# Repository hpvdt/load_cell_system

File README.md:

# Load Cell System

System to read up to six load cells and broadcast the data over USB to a host computer that would display and record it. Designed originally for testing wings for our wing profiles for lift and drag.

Hardware designed in KiCad, programmed using Arduino. Code depends on the HX711 library by [bodge](https://github.com/bogde/HX711).

The interface for the host computer is located in our [interfaces repository](https://github.com/hpvdt/interfaces) as `wing_tester`, and is based on Processing 3.

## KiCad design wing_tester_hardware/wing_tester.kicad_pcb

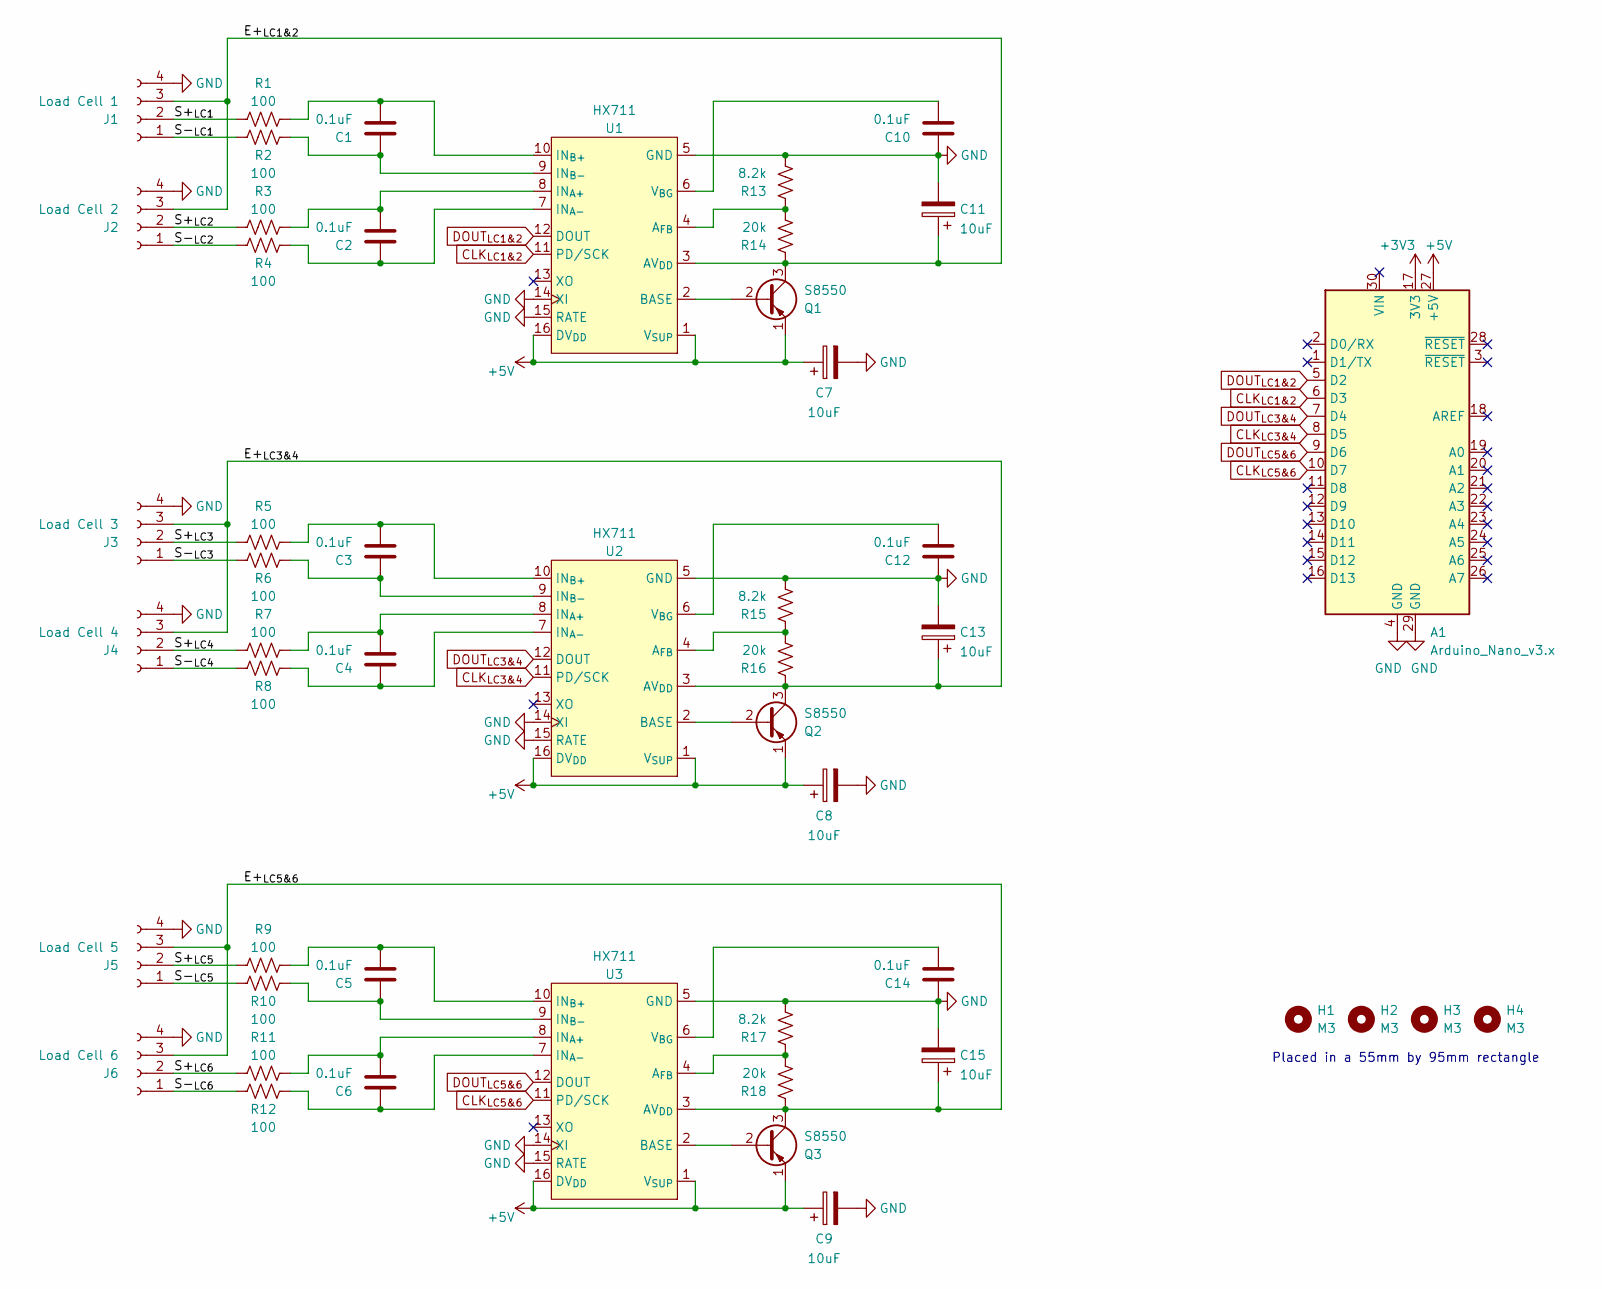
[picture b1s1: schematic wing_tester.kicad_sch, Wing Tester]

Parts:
A1: Arduino_Nano_v3.x; Arduino_Nano
C1, C2, C3, C4, C5, C6, C10, C12, C14: 0.1uF; CP_Radial_D5.0mm_P2.50mm
C7, C8, C9, C11, C13, C15: 10uF; CP_Radial_D5.0mm_P2.50mm
H1, H2, H3, H4: M3; MountingHole_3.2mm_M3_ISO7380_Pad
J1: Load Cell 1; PinHeader_1x04_P2.54mm_Vertical
J2: Load Cell 2; PinHeader_1x04_P2.54mm_Vertical
J3: Load Cell 3; PinHeader_1x04_P2.54mm_Vertical
J4: Load Cell 4; PinHeader_1x04_P2.54mm_Vertical
J5: Load Cell 5; PinHeader_1x04_P2.54mm_Vertical
J6: Load Cell 6; PinHeader_1x04_P2.54mm_Vertical
Q1, Q2, Q3: S8550; TO-92_Inline
R1, R2, R3, R4, R5, R6, R7, R8, R9, R10, R11, R12: 100; R_Axial_DIN0207_L6.3mm_D2.5mm_P10.16mm_Horizontal
R13, R15, R17: 8.2k; R_Axial_DIN0207_L6.3mm_D2.5mm_P10.16mm_Horizontal
R14, R16, R18: 20k; R_Axial_DIN0207_L6.3mm_D2.5mm_P10.16mm_Horizontal
U1, U2, U3: HX711; SOP-16_3.9x9.9mm_P1.27mm

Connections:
+3V3: A1.17 (3V3)
+5V: A1.27 (+5V), C7.1, C8.1, C9.1, Q1.1 (E), Q2.1 (E), Q3.1 (E), U1.1 (V_{SUP}), U1.16 (DV_{DD}), U2.1 (V_{SUP}), U2.16 (DV_{DD}), U3.1 (V_{SUP}), U3.16 (DV_{DD})
/E+_{LC1&2}: C11.1, J1.3, J2.3, Q1.3 (C), R14.1, U1.3 (AV_{DD})
/E+_{LC3&4}: C13.1, J3.3, J4.3, Q2.3 (C), R16.1, U2.3 (AV_{DD})
/E+_{LC5&6}: C15.1, J5.3, J6.3, Q3.3 (C), R18.1, U3.3 (AV_{DD})
/S+_{LC1}: J1.2, R1.1
/S+_{LC2}: J2.2, R3.1
/S+_{LC3}: J3.2, R5.1
/S+_{LC4}: J4.2, R7.1
/S+_{LC5}: J5.2, R9.1
/S+_{LC6}: J6.2, R11.1
/S-_{LC1}: J1.1, R2.1
/S-_{LC2}: J2.1, R4.1
/S-_{LC3}: J3.1, R6.1
/S-_{LC4}: J4.1, R8.1
/S-_{LC5}: J5.1, R10.1
/S-_{LC6}: J6.1, R12.1
CLK_{LC1&2}: A1.6 (D3), U1.11 (PD/SCK)
CLK_{LC3&4}: A1.8 (D5), U2.11 (PD/SCK)
CLK_{LC5&6}: A1.10 (D7), U3.11 (PD/SCK)
DOUT_{LC1&2}: A1.5 (D2), U1.12 (DOUT)
DOUT_{LC3&4}: A1.7 (D4), U2.12 (DOUT)
DOUT_{LC5&6}: A1.9 (D6), U3.12 (DOUT)
GND: A1.4 (GND), A1.29 (GND), C7.2, C8.2, C9.2, C10.2, C11.2, C12.2, C13.2, C14.2, C15.2, J1.4, J2.4, J3.4, J4.4, J5.4, J6.4, R13.2, R15.2, R17.2, U1.5 (GND), U1.14 (XI), U1.15 (RATE), U2.5 (GND), U2.14 (XI), U2.15 (RATE), U3.5 (GND), U3.14 (XI), U3.15 (RATE)
unnamed: C1.1, R1.2, U1.10 (IN_{B+})
unnamed: C1.2, R2.2, U1.9 (IN_{B-})
unnamed: C2.1, R3.2, U1.8 (IN_{A+})
unnamed: C2.2, R4.2, U1.7 (IN_{A-})
unnamed: C3.1, R5.2, U2.10 (IN_{B+})
unnamed: C3.2, R6.2, U2.9 (IN_{B-})
unnamed: C4.1, R7.2, U2.8 (IN_{A+})
unnamed: C4.2, R8.2, U2.7 (IN_{A-})
unnamed: C5.1, R9.2, U3.10 (IN_{B+})
unnamed: C5.2, R10.2, U3.9 (IN_{B-})
unnamed: C6.1, R11.2, U3.8 (IN_{A+})
unnamed: C6.2, R12.2, U3.7 (IN_{A-})
unnamed: C10.1, U1.6 (V_{BG})
unnamed: C12.1, U2.6 (V_{BG})
unnamed: C14.1, U3.6 (V_{BG})
unnamed: Q1.2 (B), U1.2 (BASE)
unnamed: Q2.2 (B), U2.2 (BASE)
unnamed: Q3.2 (B), U3.2 (BASE)
unnamed: R13.1, R14.2, U1.4 (A_{FB})
unnamed: R15.1, R16.2, U2.4 (A_{FB})
unnamed: R17.1, R18.2, U3.4 (A_{FB})

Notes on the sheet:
Placed in a 55mm by 95mm rectangle

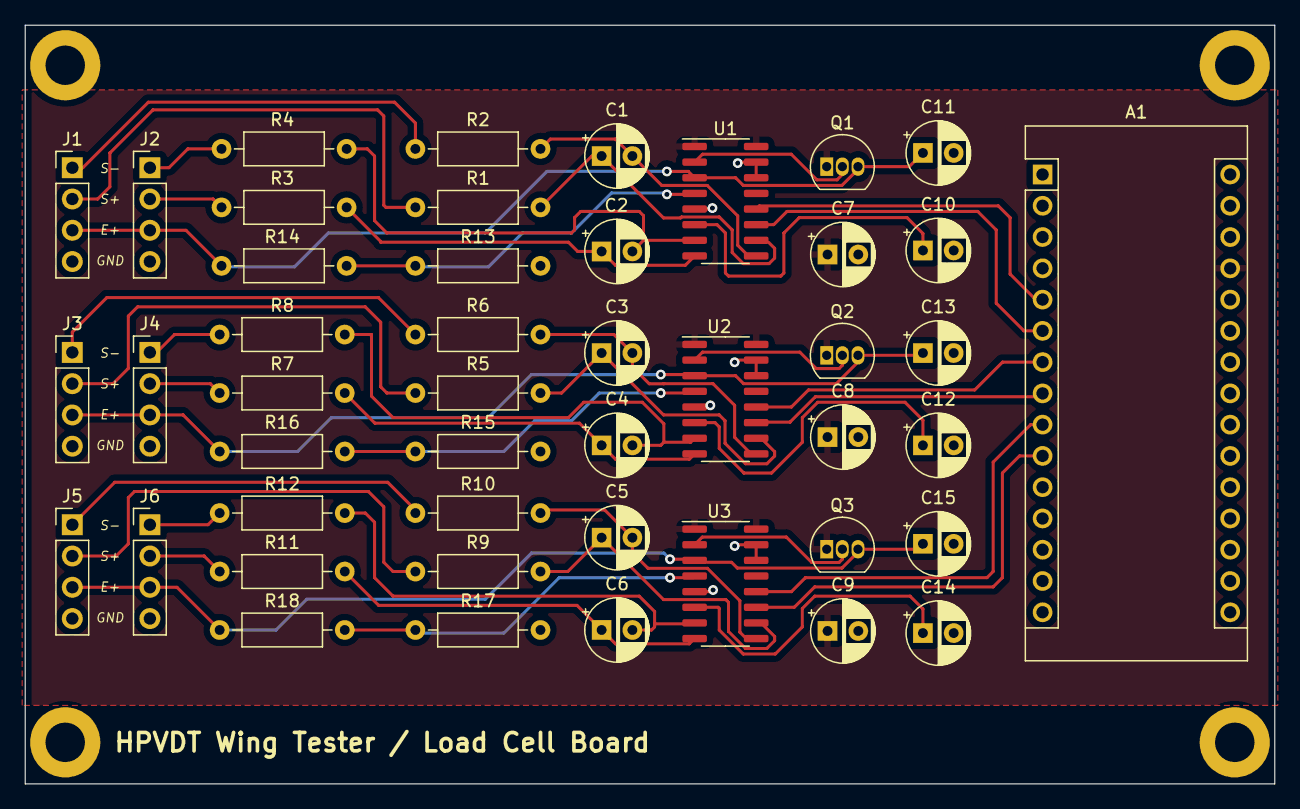
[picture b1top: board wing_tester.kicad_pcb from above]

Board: 2 copper layers, 101.5 x 61.6 mm, 50 parts (0 on the bottom side), 44 nets.

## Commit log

2022-08-02 Upload of hardware files
2022-08-02 Added microcontroller code
2023-01-05 Changed message structure
    Changed message structure so it would be more regular to parse by replacing the closing character with just the separator and using new line as the marker for a message starting
2023-01-05 Sped up read cycle
